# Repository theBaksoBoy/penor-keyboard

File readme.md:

# PENOR
### Portable Ergonomic NKRO Ortholinear Receiver

## Disclaimers
* This is just a project I made for myself, so I didn't try and make it as easy as possible for others to reproduce or anything like that. The firmware is also extremely specific to my usecase (Colemak-DH with Swedish letters and a fuck-ton of esoteric custom features). I'll try my best to write instructions as clear as possible with the time I am willing to spend on this (as I find it unlikely that anyone will see this, and thus want to actually make the keyboard).
* The case itself is decently thick (at least for a 6x3 keyboard) at a bit more than 1 cm of thickness. This is because the RP2040-Zero and TRRS-jack is underneath the PCB, thus meaning that wires will need to be soldered from the PCB to the RP2040-Zero and TRRS-jack. For this I used AWG30 copper wire, but even with this thin wire it was still a pain in the ass to put the PCB into the case and screwing it down without any wires getting pinched.
* The case was designed to allow access to the reset switch of the RP2040-Zeros at the bottom. This turned out to be completely useless, as you can't enter the bootloader on an RP2040-Zero with that button, where you are actually supposed to hold down the boot button. I had this misconception from my previous keyboard I assembled which I thought used an MCU that functioned in the same way as an RP2040-Zero. If you want to you can edit the FreeCAD model to either remove the hole or move it to where the boot button is. In any case you won't need access to the boot button as you can hold down the bootmagic keys (discussed further down) to enter the bootloader.
* The tenting isn't super stable at high tenting angles. I use linear switches with an actuation force of 50g, and altough I probably hit the buttons quite a bit harder than necessary sometimes, the keyboard is pretty unstable at the highest tenting angle, and starts tipping pretty easily. When having it on the middle tenting setting it is way more stable, however that still tip a slight bit when pressing too hard. The lowest tenting setting however is stable. If you press *really fucking hard* then I suppose that it can start leaning a bit, but even with the force that I type with this does not ever happen.

## Custom firmware features
(To see the key locations for the following features you will need to look in the source code, in qmk_firmware/keyboards/penor/keymaps/default.keymap.c, and look at the "ASCII-art" of the diffeenrt layers)
* A toggleable layer changing the main Colemak-DH layer to a QWERTY layer with the left side shifted one key to the right, so that it functions easier for games without having to rebind your keys.
* A layer that changes most of the keys to macros for common English words.
* Keys for controlling the mouse. If you quickly double-tap a direction the mouse will instantly move a ton in that direction, basically setting its position to the edge of the screen.
* Unicode mode, where you can type certain strings, which convert them to a unicode character using the Linux unicode input method of CONTROL+SHIFT+U. Pressing ESC cancels it, where as pressing SPACE or ENTER confirms which you have written. As an example, "pi" => "π".
* Recording and playing macros. Press the "record macro" key to start recording, press the "play macro" key to stop recording, or play the recording if it isn't currently recording, and press the "delay macro" button to add a 0.25 second pause when the macro gets to that recorded press during playback. The max amount of saved inputs in the macro is 256. Note that modifier keys count as two inputs; one from being pressed down, and once for being released. Note that most custom features like the word macros of common English word aren't supported in macro recordings, and won't play properly. The symbols from the symbol layer will however work.
* Key multiplication. Press the key to enter key multiplication mode. Type out a number, and then press any key, to make that key repeat that many times. Especially useful when wanting to go down n amount of rows in a document, or when wanting to replay the recorded macro a certain amount of times. Repeating a left/middle/right-click on the mouse will click the mouse at a speed of 30 CPS. If no number of repetition is specified then it will click at 30 CPS until canceled, which can be done by clicking with the mouse using the keyboard. The max amount of times a key can be multiplied is 100. If you tell it to repeat a mouse key a single time, then it will instead hold down that mouse key indefinitely until you press that mouse key again using the keyboard, which cancels it.
* A key for toggling usage of Plover (external software on the connected device). When entering and exiting the mode it will type out PHROLG to toggle Plover, where it will also toggle a layer with keys set up for Plover to work. In Plover the key bindings are tweaked a bit. Most of them are left on default, but some are changed. Since I don't know wich are default and not I will list all of the relevant bindings: 1234567890-= => #, \\ => no-op, q => #, w => T-, e => P-, r => H-, t => *, y => *, u => -F, i => -P, o => -L, p => -T, \[ => -D, \] => no-op, a => S-, s => K-, d => W-, f => R-, g => *, h => *, j => -R, k => -B, l => -G, ; => -S, ' => -Z, z => -D, x => -S, c => A-, v => O-, b => -Z, n => -E, m => -U, , => no-op, . => no-op, / => no-op, space => arpeggiate

## How to flash firmware
* **Before assembly**: Hold down the boot button whilst plugging in the RP2040-Zero to your computer.
* **After assembly**: (this works for each individual side) hold down the key in the corner that is closest to the USB-port as you are plugging the USB in.
Once you have done either of these the RP2040-Zero should appear in your file browser. Open it and place your desired firmware (.uf2 file) there, which will then flash it.

## Bill of materials
Note that this list will be for all the materials needed to create both halves of the keyboard
* 3D-printed parts. More info in the "3D-printing" section
* 1 TRRS cable
* 2 TRRS-jacks
* 2 RP2040-Zeros
* 44 THT diodes (1N4148)
* at least around 2-3 meters of loose wire (AWG30 worked pretty well for me)
* 44 Kailh Choc switches and keycaps. V1 switches are definitely compatible, but I don't know if V2 switches are or not. It's not impossible though, you would have to check the KiCad project or the gerber file of the PCB.
* 4 tenting feet. Not sure what they are called but I at least bought mine from here https://keyboard-hoarders.com/products/tenting-feet
* 4 anti-slip pads. The one included with the tenting feet from the link above are sadly too large, so I went with ones that I specifically had laying around. They were around 2.7 mm tall, and 8.5 mm in diameter. If they are a bit taller then that is fine, but its best if it isn't shorter. The diameter should probably at max be 9 mm.
* 8 M4 nuts
* 4 10 mm long M4 bolts
* 4 roughly 7 mm long M4 bolts. I just bought 10 mm long ones and cut them down extremely sloppily with a metal saw. As long as they are short enough that they can be screwed down where the PCB lies to the hole in the case without hitting the bottom, and whilst still being long enough to lock with the nut in there then its good. I don't know if this is part of the ISO standard or not, but the bolts should be the type that has a circular head that you screw down with a screwdriver. The diameter of the head can't be more than 8 mm.
* 2 PCB plates. The single design of the PCB in this repo works for both for the left and right side of the keyboard, as you just have to flip it around. Order the PCB using the gerber file in this repo and make sure that its thickness is 1.6 mm (this is the most common PCB thickness).

## 3D-printing
If you have a Creality Ender S1 (or if you think that the GCODE will still be compatible) and are using PLA or some other plastic that is printable at 200C then you don't have to worry about any of the slicing, and can just print all of the GCODE files in case/gcode/. Keep in mind the points where the print pauses where you should add nuts, and also how the printing of the logos underneath the left half should be done in a specific way. Read the instructions underneath that explains how to slice the 3D models as it explains how stuff should be done and whatnot idk.
The following files will be found in case/models/
* If you want the diode to be easier to fold for the PCB you can slice and print the "diode_folder.step". It is honestly very finicky though as I designed it to be so small.
* Slice and print "PENOR_plate_(left, but mirrorable).step", and then slice and print it again but with the model mirrored (should be possible in pretty much all slicing software... I think at least).
* Slice and print "PENOR_TRRS_holder_left.step" and "PENOR_MCU_holder_left.step", and then do it again but with both models mirrored. Note that the TRRS model can be printed without any support by making the overhanging part lay flat on the bed. The MCU holder model should be oriented so that the slight overhanging part is on top (the same orientation that it will have in the assembly). This of course requires some support material under the overhang, but support material isn't needed anywhere else for that model.
* Mirror "PENOR_right_main_UNMIRRORED.step" as you slice it, and make sure that it pauses on the layer just before the hole for the nut where the PCB will be screwed in gets covered, where you should add nuts into the two holes before resuming the print. Also make sure to add support material where the anti-slip pads will be. If you also aren't sure if the bridge done where the tenting feet will sit will be able to be printed without drooping then you can also make a line of support material along the center of the hole.
* Slice and print "PENOR_left_white.step", "PENOR_left_orange.step", and "PENOR_left_main.step" right after each other as shown in this video https://youtu.be/m_SXRGGoTQo, to make it possible to print the logos at the bottom with two different colors from the color used for the main part of the case. Remember to also add the pause for the nuts and the necessary cupport material on the left half of the case too!

## Assembly instructions
1. Before assembling anything you should already flash the firmware to BOTH of your RP2040-Zeros, as it contains logic for allowing to enter the bootloader without the usage of the boot button which won't be acessible in the finished assembly. Just hold down the boot button whilst plugging it into your computer, and it should appear in your file manager. Place the .uf2 file from this repo (or compile the firmware yourself) into the RP2040-Zeros. If your RP2040-Zeros has "perferations" on the edges from when it was snapped of from a larger board then you should sand these down so that the edges of the board are flat, as otherwise they won't fit properly in the case.
2. Solder all the diodes to the PCB. Remember to look at the icons on the PCB that specify what direction the diodes should have so that you don't acidentally assemble some in the wrong direction, as sometimes the direction is different from what you might expect (almost all point downwards, however a few point up). Once soldered, clip the legs so that they are pretty short, so that they fit for the next step.
3. On the side that has the leg joints, put the 3D-printed switch plate on the PCB, and put all of the switches through the switch plate and PCB, and then solder all of the switches to the PCB.
4. Solder loose wires to every hole on the PCB that is labeled as "row n" and "col n" (where n is a number). In total you should have 10 loose wires. The longer they are, the more you will want to shoot yourself when trying to assemble the plate with the case without any wires being in the way, however if they are too short then everything will be extremely tight. I recommend making the wires furthest away from where the RP2040-Zero will be in the case be around 10 cm, where the closest ones can be around 6 cm or so. For the left half I made ALL of the wires 15 cm long and the walls in my room almost became red.
5. Solder wires from the RP2040-Zero to the TRRS-jack. Remember to look at how the RP2040-Zero will lay in the case to ensure that you solder the wires onto the pins in ways that the wires will actually be able to lay in so that they don't have to make any really sharp turns, concidering how there is a wall directly next to the RP2040-Zero on one side (don't forget that the side the wall is on changes for each half of the keyboard!). You need three wires for this, which I recommend making around 10 cm. Technically the legs you decide to use for the TRRS-jack doesn't matter *as long as you do the same for both halves*, but I'll say which ones I used. Remember to try and solder it to the legs so that the solder is on the inside of the legs and not the outside, so that the jack can lay flat without the solder being in the way. Also make note of how the jacks will sit in the case, so that you solder the wires to go in the correct direction so that they don't have to bend sharply.
    1. Solder a wire from the **GND** pin to the leg that is alone on its side.
    2. Solder a second wire from the **3V3** pin to the leg that is the closest to the leg you previously soldered to.
    3. Solder the last wire from **pin 0** to the leg that is next to the second leg you soldered to.
6. If you are assembling the left half (and ONLY if it is the left half), solder a short wire from **3V3** to **pin 29**. This is to make it able to tell that it is the left half of the keyboard automatically.
7. Solder all of the wires onto the RP2040-Zero. Remember to concider the walls to make the wires not have to make any really sharp turns by the pins. Also remember to concider how the part that will hold down the RP2040-Zero will cover up the pins at the bottom, which will thus also to some extent be like a wall that needs to be router around.
   * col0 -> pin 2
   * col1 -> pin 3
   * col2 -> pin 4
   * col3 -> pin 5
   * col4 -> pin 6
   * col5 -> pin 7
   * row0 -> pin 15
   * row1 -> pin 26
   * row2 -> pin 27
   * row3 -> pin 28
8. Put the TRRS-jack by its hole in the case. Add a nut to the hole next to it, and use a bolt to screw the small 3D-printed part that holds it in place. Then put the RP2040-Zero where it should be in the case, add a nut to the 3D-printed part that holds it down, and fasten it with a bolt. If you have no clue which parts are supposed to be used for this then you can look in the FreeCAD model in this repo and see the location of all the parts.
9. Put the PCB onto the case, making sure that no wires are getting pinched between the PCB and the case. You will most likely need some long and slim object like a chopstick to try and nudge wires away from areas that the PCB will lay on as you put the PCB on. Once there is no wobble, or at least extremely minimal wobble, you can screw the two bolts into the holes in the PCB. If you have printed the case in black like shown in the image at the top of this file then you can optionally put electrical tape onto the screw heads. It does't look absolutely perfect, but it does make it look way neater than seeing two big-ass silvery bolt heads between your keys.
10. Do a happy little dance (IMPORTANT! Only do this if the keyboard works correctly).

## Compiling firmwre (not needed if you just use the qmk_firmware/keyboards/penor/penor_default.uf2 file)
1. Use QMK Firmware 0.23.7. Different versions might work, however it should for sure work on this version.
2. copy over the directory qmk_firmware/... to the directory where your qmk_firmware is located, making it so that the penor/... is inside of your qmk_firmware/keyboards.
3. Make sure that your working directory in the terminal is the qmk_firmware directory, and then run the command

    make penor:default

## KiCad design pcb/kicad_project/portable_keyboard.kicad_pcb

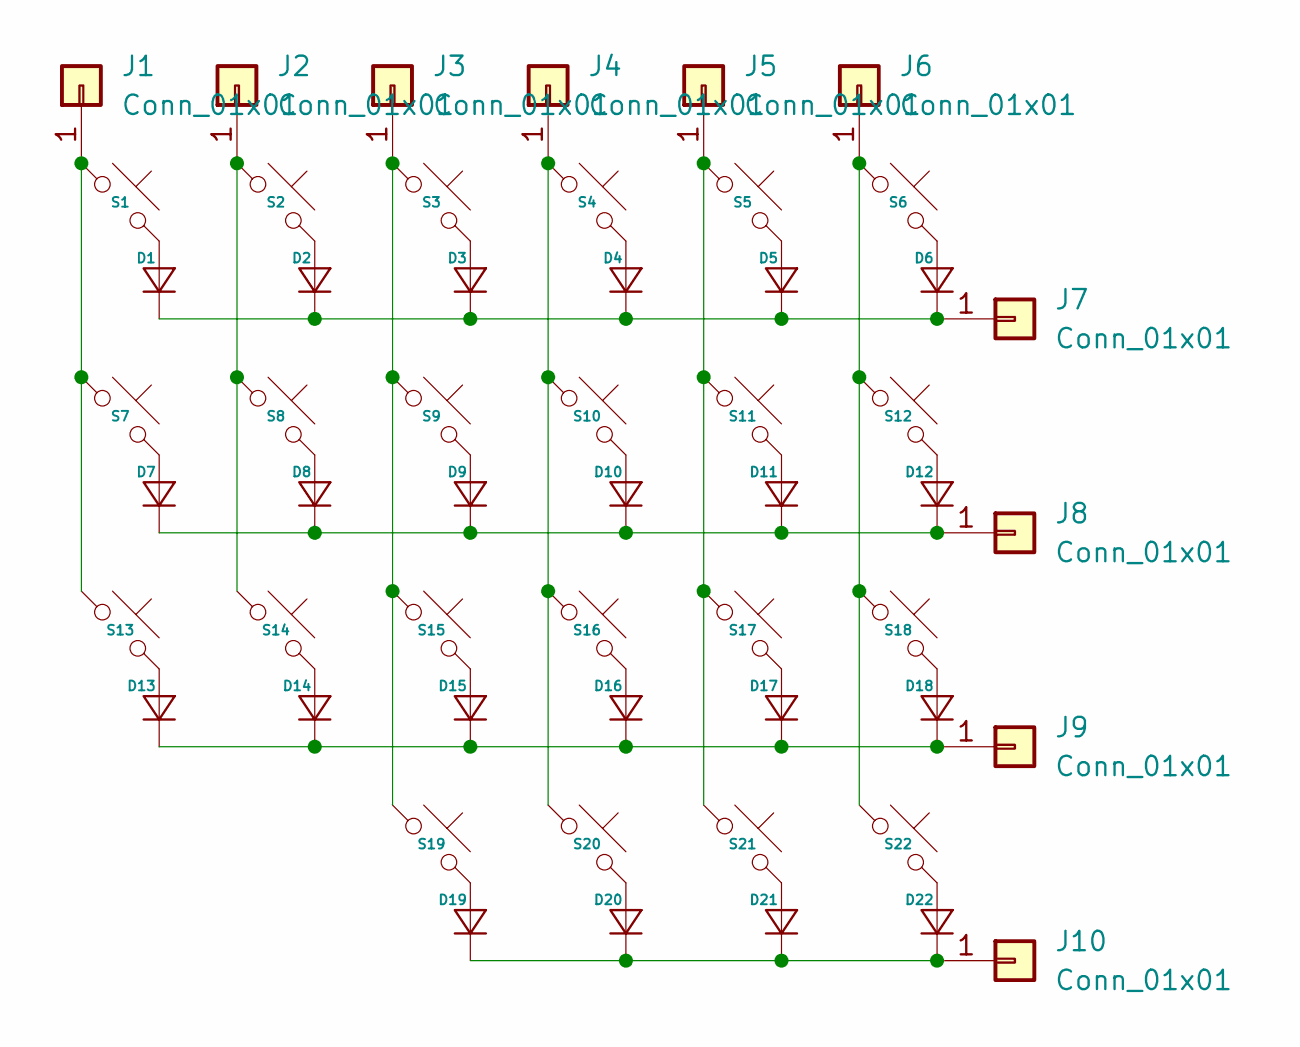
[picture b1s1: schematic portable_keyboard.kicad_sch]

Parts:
D1, D2, D3, D4, D5, D6, D7, D8, D9, D10, D11, D12, D13, D14, D15, D16, D17, D18, D19, D20, D21, D22: Diode_DO-35
J1, J2, J3, J4, J5, J6, J7, J8, J9, J10: Conn_01x01; TestPoint
S1, S2, S3, S4, S5, S6, S7, S8, S9, S10, S11, S12, S13, S14, S15, S16, S17, S18, S19, S20, S21, S22: SW_PG1350_reversible

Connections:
unnamed: D1.2 (A), S1.2
unnamed: D1.1 (K), D2.1 (K), D3.1 (K), D4.1 (K), D5.1 (K), D6.1 (K), J7.1
unnamed: D2.2 (A), S2.2
unnamed: D3.2 (A), S3.2
unnamed: D4.2 (A), S4.2
unnamed: D5.2 (A), S5.2
unnamed: D6.2 (A), S6.2
unnamed: D7.2 (A), S7.2
unnamed: D8.2 (A), S8.2
unnamed: D9.2 (A), S9.2
unnamed: D10.2 (A), S10.2
unnamed: D7.1 (K), D8.1 (K), D9.1 (K), D10.1 (K), D11.1 (K), D12.1 (K), J8.1
unnamed: D11.2 (A), S11.2
unnamed: D12.2 (A), S12.2
unnamed: D13.2 (A), S13.2
unnamed: D13.1 (K), D14.1 (K), D15.1 (K), D16.1 (K), D17.1 (K), D18.1 (K), J9.1
unnamed: D14.2 (A), S14.2
unnamed: D15.2 (A), S15.2
unnamed: D16.2 (A), S16.2
unnamed: D17.2 (A), S17.2
unnamed: D18.2 (A), S18.2
unnamed: D19.2 (A), S19.2
unnamed: D19.1 (K), D20.1 (K), D21.1 (K), D22.1 (K), J10.1
unnamed: D20.2 (A), S20.2
unnamed: D21.2 (A), S21.2
unnamed: D22.2 (A), S22.2
unnamed: J1.1, S1.1, S7.1, S13.1
unnamed: J2.1, S2.1, S8.1, S14.1
unnamed: J3.1, S3.1, S9.1, S15.1, S19.1
unnamed: J4.1, S4.1, S10.1, S16.1, S20.1
unnamed: J5.1, S5.1, S11.1, S17.1, S21.1
unnamed: J6.1, S6.1, S12.1, S18.1, S22.1

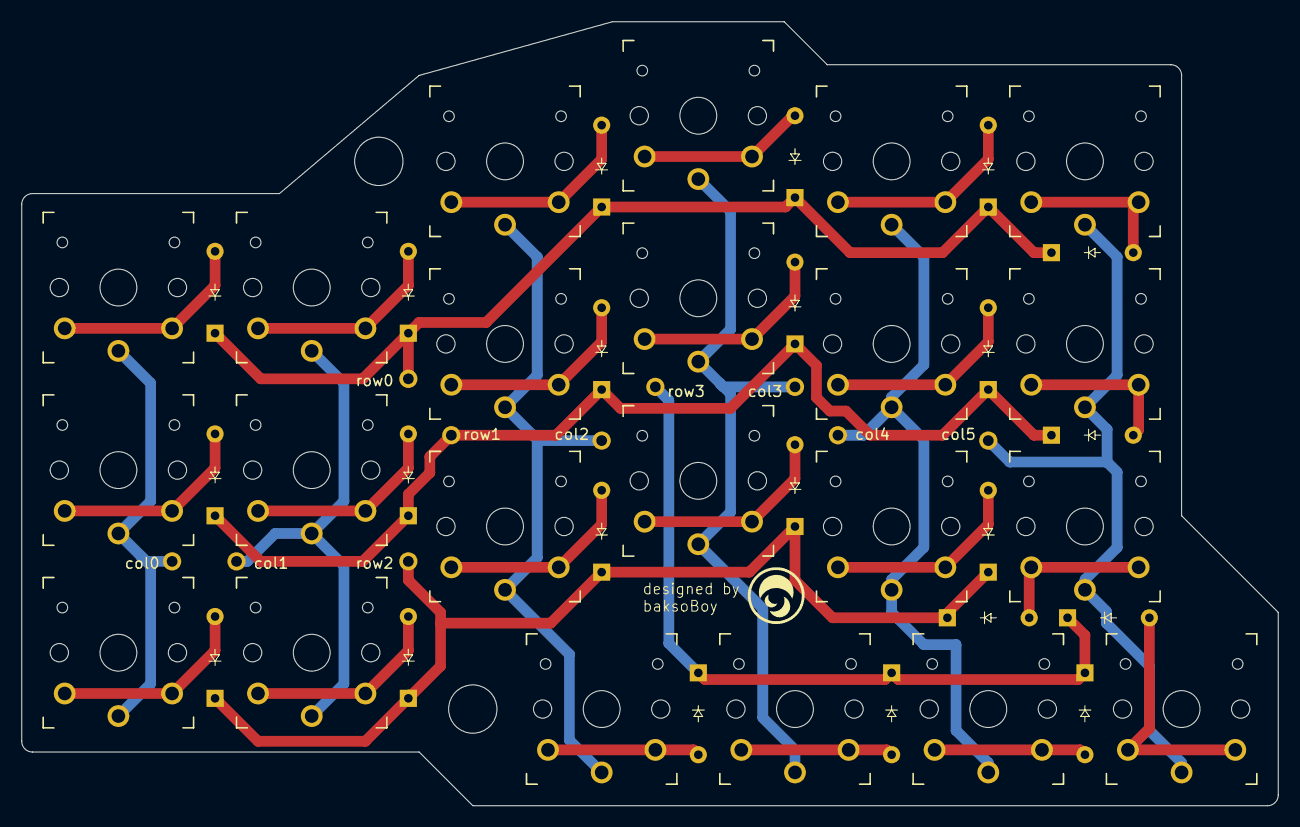
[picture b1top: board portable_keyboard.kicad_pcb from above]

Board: 2 copper layers, 117.0 x 73.0 mm, 54 parts (0 on the bottom side), 32 nets.

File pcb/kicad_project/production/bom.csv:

Designator,Footprint,Quantity,Value,LCSC Part #
"D1, D10, D11, D12, D13, D14, D15, D16, D17, D18, D19, D2, D20, D21, D22, D3, D4, D5, D6, D7, D8, D9",Diode_DO-35,22,~,
"J1, J10, J2, J3, J4, J5, J6, J7, J8, J9",TestPoint,10,Conn_01x01,
"S1, S10, S11, S12, S13, S14, S15, S16, S17, S18, S19, S2, S20, S21, S22, S3, S4, S5, S6, S7, S8, S9",SW_PG1350_reversible,22,~,

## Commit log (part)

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2026-03-01 Added more layers. Still only half-functioning though
2026-03-25 tweaked shit although currently broken
2026-03-26 fix keymap ordering
2026-03-26 set up bootmagic
2026-03-27 fix indices for thumb keys on right half
2026-03-27 make sure firmware uses soft sereal instead of I^2C... I think
2026-03-27 fix file being uploaded in wrong directory
2026-03-27 ensure serial wiring is used or something idfk
2026-03-28 define SPLIT_USB_DETECT
2026-03-28 change pin used for soft serial from 1 to 0
2026-03-28 change method for entering bootloader on right half
    apparently the bootmagic feature for being able to specify what key to use for it, where you can also have a different key for the right half of the keyboard, is deprecated for some reason (even thou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
2026-03-28 move gaming layer toggle to prevent acidental presses
2026-03-28 add image used in readme
2026-03-28 got bootmagic to work properly on both halves. The documentation was just bullshit
2026-03-28 make control and shift work when in mouse layer
2026-03-29 key multiplication in progress
2026-03-29 add case files
2026-03-29 add gerber and kicad project
2026-03-30 get key multiplication to work with most keys
    The only thing missing from it now (I think) is using it to activate auto clickers
2026-03-30 finish key multiplication logic (auto clickers)
2026-03-30 implement Plover toggling when toggling steno
2026-03-31 remove redundant main/gaming layer toggle
2026-03-31 add unicode input mode with a bunch of symbols
2026-04-01 improve steno toggle
2026-04-01 fix mistakes from steno tweak
2026-04-02 add mouse warping
2026-04-02 add em-dash to unicode input
2026-04-02 add more unicode input characters
2026-04-03 add macro recording and playing feature
2026-04-03 add qmk version comment
2026-04-04 add support for macro playing with the key multiplication feature
2026-04-04 remove unnecessary manual keycode
2026-04-12 changed mouse-warping functionality
2026-05-17 made ESC possible to input with left half
2026-05-20 tweaked unicode name for checkbox and tweaked code spacing
